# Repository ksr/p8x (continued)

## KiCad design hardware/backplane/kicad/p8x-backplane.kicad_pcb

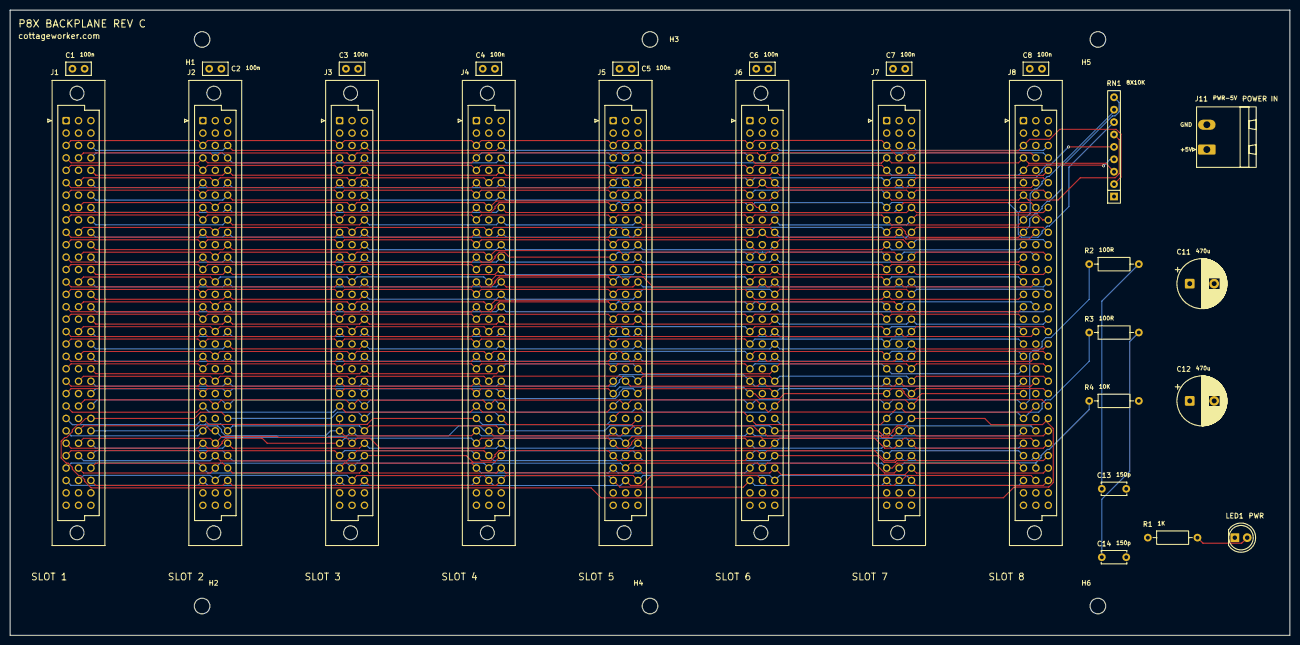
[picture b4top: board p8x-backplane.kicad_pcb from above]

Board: 4 copper layers, 262.0 x 128.0 mm, 33 parts (0 on the bottom side), 77 nets.

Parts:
C1, C2, C3, C4, C5, C6, C7, C8: 100nF; C_Disc_D5.0mm_W2.5mm_P2.50mm
C11, C12: 470uF; CP_Radial_D10.0mm_P5.00mm
C13, C14: 150pF; C_Disc_D5.0mm_W2.5mm_P5.00mm
H1, H2, H3, H4, H5, H6: MountingHole_3.2mm_M3
J1: SLOT1; DIN41612_C_3x32_Female_Vertical_THT
J2: SLOT2; DIN41612_C_3x32_Female_Vertical_THT
J3: SLOT3; DIN41612_C_3x32_Female_Vertical_THT
J4: SLOT4; DIN41612_C_3x32_Female_Vertical_THT
J5: SLOT5; DIN41612_C_3x32_Female_Vertical_THT
J6: SLOT6; DIN41612_C_3x32_Female_Vertical_THT
J7: SLOT7; DIN41612_C_3x32_Female_Vertical_THT
J8: SLOT8; DIN41612_C_3x32_Female_Vertical_THT
J11: PWR-5V; PhoenixContact_MSTBA_2,5_2-G-5,08_1x02_P5.08mm_Horizontal
LED1: PWR; LED_D5.0mm
R1: 1K; R_Axial_DIN0207_L6.3mm_D2.5mm_P10.16mm_Horizontal
R2, R3: 100R; R_Axial_DIN0207_L6.3mm_D2.5mm_P10.16mm_Horizontal
R4: 10K; R_Axial_DIN0207_L6.3mm_D2.5mm_P10.16mm_Horizontal
RN1: 8X10K; R_Array_SIP9

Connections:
-RES: J1.a11, J2.a11, J3.a11, J4.a11, J5.a11, J6.a11, J7.a11, J8.a11
A0: J1.c3, J2.c3, J3.c3, J4.c3, J5.c3, J6.c3, J7.c3, J8.c3
A1: J1.c4, J2.c4, J3.c4, J4.c4, J5.c4, J6.c4, J7.c4, J8.c4
A2: J1.c5, J2.c5, J3.c5, J4.c5, J5.c5, J6.c5, J7.c5, J8.c5
A3: J1.c6, J2.c6, J3.c6, J4.c6, J5.c6, J6.c6, J7.c6, J8.c6
A4: J1.c7, J2.c7, J3.c7, J4.c7, J5.c7, J6.c7, J7.c7, J8.c7
A5: J1.c8, J2.c8, J3.c8, J4.c8, J5.c8, J6.c8, J7.c8, J8.c8
A6: J1.c9, J2.c9, J3.c9, J4.c9, J5.c9, J6.c9, J7.c9, J8.c9
A7: J1.c10, J2.c10, J3.c10, J4.c10, J5.c10, J6.c10, J7.c10, J8.c10
A8: J1.c11, J2.c11, J3.c11, J4.c11, J5.c11, J6.c11, J7.c11, J8.c11
A9: J1.c12, J2.c12, J3.c12, J4.c12, J5.c12, J6.c12, J7.c12, J8.c12
A10: J1.c13, J2.c13, J3.c13, J4.c13, J5.c13, J6.c13, J7.c13, J8.c13
A11: J1.c14, J2.c14, J3.c14, J4.c14, J5.c14, J6.c14, J7.c14, J8.c14
A12: J1.c15, J2.c15, J3.c15, J4.c15, J5.c15, J6.c15, J7.c15, J8.c15
A13: J1.c16, J2.c16, J3.c16, J4.c16, J5.c16, J6.c16, J7.c16, J8.c16
A14: J1.c17, J2.c17, J3.c17, J4.c17, J5.c17, J6.c17, J7.c17, J8.c17
A15: J1.c18, J2.c18, J3.c18, J4.c18, J5.c18, J6.c18, J7.c18, J8.c18
ALUM: J1.c23, J2.c23, J3.c23, J4.c23, J5.c23, J6.c23, J7.c23, J8.c23
ALUS0: J1.c19, J2.c19, J3.c19, J4.c19, J5.c19, J6.c19, J7.c19, J8.c19
ALUS1: J1.c20, J2.c20, J3.c20, J4.c20, J5.c20, J6.c20, J7.c20, J8.c20
ALUS2: J1.c21, J2.c21, J3.c21, J4.c21, J5.c21, J6.c21, J7.c21, J8.c21
ALUS3: J1.c22, J2.c22, J3.c22, J4.c22, J5.c22, J6.c22, J7.c22, J8.c22
BSEL: J1.b28, J2.b28, J3.b28, J4.b28, J5.b28, J6.b28, J7.b28, J8.b28
CIN: J1.c24, J2.c24, J3.c24, J4.c24, J5.c24, J6.c24, J7.c24, J8.c24
CLK: J1.a24, J2.a24, J3.a24, J4.a24, J5.a24, J6.a24, J7.a24, J8.a24, R2.1
CLKB: J1.a25, J2.a25, J3.a25, J4.a25, J5.a25, J6.a25, J7.a25, J8.a25, R3.1
CLKB_T: C14.1, R3.2
CLK_T: C13.1, R2.2
CLRC: J1.b27, J2.b27, J3.b27, J4.b27, J5.b27, J6.b27, J7.b27, J8.b27
D0: J1.a3, J2.a3, J3.a3, J4.a3, J5.a3, J6.a3, J7.a3, J8.a3, RN1.2
D1: J1.a4, J2.a4, J3.a4, J4.a4, J5.a4, J6.a4, J7.a4, J8.a4, RN1.3
D2: J1.a5, J2.a5, J3.a5, J4.a5, J5.a5, J6.a5, J7.a5, J8.a5, RN1.4
D3: J1.a6, J2.a6, J3.a6, J4.a6, J5.a6, J6.a6, J7.a6, J8.a6, RN1.5
D4: J1.a7, J2.a7, J3.a7, J4.a7, J5.a7, J6.a7, J7.a7, J8.a7, RN1.6
D5: J1.a8, J2.a8, J3.a8, J4.a8, J5.a8, J6.a8, J7.a8, J8.a8, RN1.7
D6: J1.a9, J2.a9, J3.a9, J4.a9, J5.a9, J6.a9, J7.a9, J8.a9, RN1.8
D7: J1.a10, J2.a10, J3.a10, J4.a10, J5.a10, J6.a10, J7.a10, J8.a10, RN1.9
DLD0: J1.a16, J2.a16, J3.a16, J4.a16, J5.a16, J6.a16, J7.a16, J8.a16
DLD1: J1.a17, J2.a17, J3.a17, J4.a17, J5.a17, J6.a17, J7.a17, J8.a17
DLD2: J1.a18, J2.a18, J3.a18, J4.a18, J5.a18, J6.a18, J7.a18, J8.a18
DLD3: J1.a19, J2.a19, J3.a19, J4.a19, J5.a19, J6.a19, J7.a19, J8.a19
DOE0: J1.a12, J2.a12, J3.a12, J4.a12, J5.a12, J6.a12, J7.a12, J8.a12
DOE1: J1.a13, J2.a13, J3.a13, J4.a13, J5.a13, J6.a13, J7.a13, J8.a13
DOE2: J1.a14, J2.a14, J3.a14, J4.a14, J5.a14, J6.a14, J7.a14, J8.a14
DOE3: J1.a15, J2.a15, J3.a15, J4.a15, J5.a15, J6.a15, J7.a15, J8.a15
FC: J1.a27, J2.a27, J3.a27, J4.a27, J5.a27, J6.a27, J7.a27, J8.a27
FN: J1.a29, J2.a29, J3.a29, J4.a29, J5.a29, J6.a29, J7.a29, J8.a29
FV: J1.a30, J2.a30, J3.a30, J4.a30, J5.a30, J6.a30, J7.a30, J8.a30
FZ: J1.a28, J2.a28, J3.a28, J4.a28, J5.a28, J6.a28, J7.a28, J8.a28
GND: C1.2, C2.2, C3.2, C4.2, C5.2, C6.2, C7.2, C8.2, C11.2, C12.2, C13.2, C14.2, J1.a31, J1.a32, J1.b3, J1.b5, J1.b7, J1.b9, J1.b11, J1.b13, J1.b15, J1.b17, J1.b19, J1.b21, J1.b23, J1.b25, J1.b31, J1.b32, J1.c31, J1.c32, J2.a31, J2.a32, J2.b3, J2.b5, J2.b7, J2.b9, J2.b11, J2.b13, J2.b15, J2.b17, J2.b19, J2.b21, J2.b23, J2.b25, J2.b31, J2.b32, J2.c31, J2.c32, J3.a31, J3.a32, J3.b3, J3.b5, J3.b7, J3.b9, J3.b11, J3.b13, J3.b15, J3.b17, J3.b19, J3.b21, J3.b23, J3.b25, J3.b31, J3.b32, J3.c31, J3.c32, J4.a31, J4.a32, J4.b3, J4.b5, J4.b7, J4.b9, J4.b11, J4.b13, J4.b15, J4.b17, J4.b19, J4.b21, J4.b23, J4.b25, J4.b31, J4.b32, J4.c31, J4.c32, J5.a31, J5.a32, J5.b3, J5.b5, J5.b7, J5.b9, J5.b11, J5.b13, J5.b15, J5.b17, J5.b19, J5.b21, J5.b23, J5.b25, J5.b31, J5.b32, J5.c31, J5.c32, J6.a31, J6.a32, J6.b3, J6.b5, J6.b7, J6.b9, J6.b11, J6.b13, J6.b15, J6.b17, J6.b19, J6.b21, J6.b23, J6.b25, J6.b31, J6.b32, J6.c31, J6.c32, J7.a31, J7.a32, J7.b3, J7.b5, J7.b7, J7.b9, J7.b11, J7.b13, J7.b15, J7.b17, J7.b19, J7.b21, J7.b23, J7.b25, J7.b31, J7.b32, J7.c31, J7.c32, J8.a31, J8.a32, J8.b3, J8.b5, J8.b7, J8.b9, J8.b11, J8.b13, J8.b15, J8.b17, J8.b19, J8.b21, J8.b23, J8.b25, J8.b31, J8.b32, J8.c31, J8.c32, J11.2, LED1.1
IRQ: J1.b29, J2.b29, J3.b29, J4.b29, J5.b29, J6.b29, J7.b29, J8.b29, R4.1
LDF: J1.a26, J2.a26, J3.a26, J4.a26, J5.a26, J6.a26, J7.a26, J8.a26
LDZN: J1.c28, J2.c28, J3.c28, J4.c28, J5.c28, J6.c28, J7.c28, J8.c28
LED_A: LED1.2, R1.2
PDEC: J1.a23, J2.a23, J3.a23, J4.a23, J5.a23, J6.a23, J7.a23, J8.a23
PINC: J1.a22, J2.a22, J3.a22, J4.a22, J5.a22, J6.a22, J7.a22, J8.a22
PSEL0: J1.a20, J2.a20, J3.a20, J4.a20, J5.a20, J6.a20, J7.a20, J8.a20
PSEL1: J1.a21, J2.a21, J3.a21, J4.a21, J5.a21, J6.a21, J7.a21, J8.a21
PSEL2: J1.c27, J2.c27, J3.c27, J4.c27, J5.c27, J6.c27, J7.c27, J8.c27
SETC: J1.c30, J2.c30, J3.c30, J4.c30, J5.c30, J6.c30, J7.c30, J8.c30
SH0: J1.c25, J2.c25, J3.c25, J4.c25, J5.c25, J6.c25, J7.c25, J8.c25
SH1: J1.c26, J2.c26, J3.c26, J4.c26, J5.c26, J6.c26, J7.c26, J8.c26
SHCIN: J1.c29, J2.c29, J3.c29, J4.c29, J5.c29, J6.c29, J7.c29, J8.c29
SPARE11: J1.b30, J2.b30, J3.b30, J4.b30, J5.b30, J6.b30, J7.b30, J8.b30
SPARE12: J1.b4, J2.b4, J3.b4, J4.b4, J5.b4, J6.b4, J7.b4, J8.b4
SPARE13: J1.b6, J2.b6, J3.b6, J4.b6, J5.b6, J6.b6, J7.b6, J8.b6
SPARE14: J1.b8, J2.b8, J3.b8, J4.b8, J5.b8, J6.b8, J7.b8, J8.b8
SPARE15: J1.b10, J2.b10, J3.b10, J4.b10, J5.b10, J6.b10, J7.b10, J8.b10
SPARE16: J1.b12, J2.b12, J3.b12, J4.b12, J5.b12, J6.b12, J7.b12, J8.b12
SPARE17: J1.b14, J2.b14, J3.b14, J4.b14, J5.b14, J6.b14, J7.b14, J8.b14
SPARE18: J1.b16, J2.b16, J3.b16, J4.b16, J5.b16, J6.b16, J7.b16, J8.b16
SPARE19: J1.b18, J2.b18, J3.b18, J4.b18, J5.b18, J6.b18, J7.b18, J8.b18
SPARE20: J1.b20, J2.b20, J3.b20, J4.b20, J5.b20, J6.b20, J7.b20, J8.b20
SPARE21: J1.b22, J2.b22, J3.b22, J4.b22, J5.b22, J6.b22, J7.b22, J8.b22
SPARE22: J1.b24, J2.b24, J3.b24, J4.b24, J5.b24, J6.b24, J7.b24, J8.b24
SPARE23: J1.b26, J2.b26, J3.b26, J4.b26, J5.b26, J6.b26, J7.b26, J8.b26
VCC: C1.1, C2.1, C3.1, C4.1, C5.1, C6.1, C7.1, C8.1, C11.1, C12.1, J1.a1, J1.a2, J1.b1, J1.b2, J1.c1, J1.c2, J2.a1, J2.a2, J2.b1, J2.b2, J2.c1, J2.c2, J3.a1, J3.a2, J3.b1, J3.b2, J3.c1, J3.c2, J4.a1, J4.a2, J4.b1, J4.b2, J4.c1, J4.c2, J5.a1, J5.a2, J5.b1, J5.b2, J5.c1, J5.c2, J6.a1, J6.a2, J6.b1, J6.b2, J6.c1, J6.c2, J7.a1, J7.a2, J7.b1, J7.b2, J7.c1, J7.c2, J8.a1, J8.a2, J8.b1, J8.b2, J8.c1, J8.c2, J11.1, R1.1, R4.2, RN1.1

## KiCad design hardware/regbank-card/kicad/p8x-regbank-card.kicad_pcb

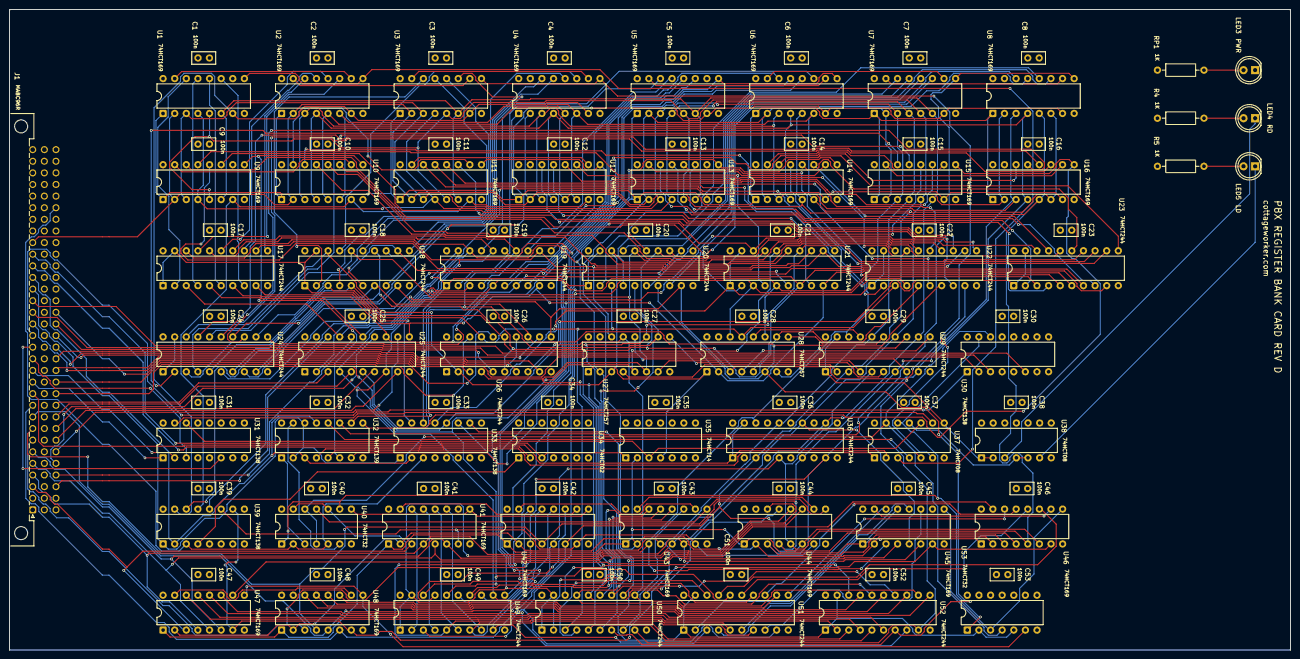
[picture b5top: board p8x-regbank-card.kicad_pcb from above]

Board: 4 copper layers, 280.0 x 140.0 mm, 113 parts (0 on the bottom side), 221 nets.

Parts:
C1, C2, C3, C4, C5, C6, C7, C8, C9, C10, C11, C12, C13, C14, C15, C16, C17, C18, C19, C20, C21, C22, C23, C24, C25, C26, C27, C28, C29, C30, C31, C32, C33, C34, C35, C36, C37, C38, C39, C40, C41, C42, C43, C44, C45, C46, C47, C48, C49, C50, C51, C52, C53: 100nF; C_Disc_D5.0mm_W2.5mm_P2.50mm
J1: MABC96R; DIN41612_C_3x32_Male_Horizontal_THT
LED3, LED4: GRN; LED_D5.0mm
LED5: YEL; LED_D5.0mm
R4, R5: 1K; R_Axial_DIN0207_L6.3mm_D2.5mm_P10.16mm_Horizontal
RP1: 1K; R_Axial_DIN0207_L6.3mm_D2.5mm_P10.16mm_Horizontal
U1, U2, U3, U4, U5, U6, U7, U8, U9, U10, U11, U12, U13, U14, U15, U16, U41, U42, U43, U44, U45, U46, U47, U48: 74HCT169; DIP-16_W7.62mm
U17, U18, U19, U20, U21, U22, U23, U24, U25, U26, U29, U36, U49, U50, U51, U52: 74HCT244; DIP-20_W7.62mm
U27, U28: 74HCT257; DIP-16_W7.62mm
U30, U31, U33, U39: 74HCT138; DIP-16_W7.62mm
U32: 74HCT139; DIP-16_W7.62mm
U34: 74HCT02; DIP-14_W7.62mm
U35: 74HCT14; DIP-14_W7.62mm
U37, U38: 74HCT08; DIP-14_W7.62mm
U40, U53: 74HCT32; DIP-14_W7.62mm

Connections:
-CNT0: U1.7, U2.7, U3.7, U4.7, U39.15
-CNT1: U5.7, U6.7, U7.7, U8.7, U39.14
-CNT2: U9.7, U10.7, U11.7, U12.7, U39.13
-CNT3: U13.7, U14.7, U15.7, U16.7, U39.12
-CNT4: U39.11, U41.7, U42.7, U43.7, U44.7
-CNT5: U39.10, U45.7, U46.7, U47.7, U48.7
-LDH: U30.14, U37.13, U40.4, U40.12, U53.4
-LDH0: U32.12, U37.4
-LDH0E: U3.9, U4.9, U37.6
-LDH1: U7.9, U8.9, U32.11
-LDH2: U11.9, U12.9, U32.10
-LDH3: U15.9, U16.9, U32.9
-LDH4: U40.11, U43.9, U44.9
-LDH5: U47.9, U48.9, U53.6
-LDHG: U32.15, U40.6
-LDL: U30.15, U37.12, U40.1, U40.9, U53.1
-LDL0: U32.4, U37.1
-LDL0E: U1.9, U2.9, U37.3
-LDL1: U5.9, U6.9, U32.5
-LDL2: U9.9, U10.9, U32.6
-LDL3: U13.9, U14.9, U32.7
-LDL4: U40.8, U41.9, U42.9
-LDL5: U45.9, U46.9, U53.3
-LDLG: U32.1, U40.3
-LDP: U37.11, U38.4, U38.5
-POE: U29.1, U29.19, U37.8, U38.1, U38.2
-POEH: U31.14, U35.3, U37.10
-POEL: U31.15, U37.9
-RES: J1.a11, U36.1, U36.19, U37.2, U37.5
-SEL0: U17.1, U17.19, U18.1, U18.19, U33.15
-SEL1: U19.1, U19.19, U20.1, U20.19, U33.14
-SEL2: U21.1, U21.19, U22.1, U22.19, U33.13
-SEL3: U23.1, U23.19, U24.1, U24.19, U33.12
-SEL4: U33.11, U40.10, U40.13, U49.1, U49.19, U50.1, U50.19
-SEL5: U33.10, U51.1, U51.19, U52.1, U52.19, U53.2, U53.5
A0: J1.c3, U25.18
A1: J1.c4, U25.16
A2: J1.c5, U25.14
A3: J1.c6, U25.12
A4: J1.c7, U25.9
A5: J1.c8, U25.7
A6: J1.c9, U25.5
A7: J1.c10, U25.3
A8: J1.c11, U26.18
A9: J1.c12, U26.16
A10: J1.c13, U26.14
A11: J1.c14, U26.12
A12: J1.c15, U26.9
A13: J1.c16, U26.7
A14: J1.c17, U26.5
A15: J1.c18, U26.3
CLK: J1.a24, U1.2, U2.2, U3.2, U4.2, U5.2, U6.2, U7.2, U8.2, U9.2, U10.2, U11.2, U12.2, U13.2, U14.2, U15.2, U16.2, U41.2, U42.2, U43.2, U44.2, U45.2, U46.2, U47.2, U48.2
CNTN: U34.1, U39.4
D0: J1.a3, U1.3, U3.3, U5.3, U7.3, U9.3, U11.3, U13.3, U15.3, U29.18, U36.18, U41.3, U43.3, U45.3, U47.3
D1: J1.a4, U1.4, U3.4, U5.4, U7.4, U9.4, U11.4, U13.4, U15.4, U29.16, U36.16, U41.4, U43.4, U45.4, U47.4
D2: J1.a5, U1.5, U3.5, U5.5, U7.5, U9.5, U11.5, U13.5, U15.5, U29.14, U36.14, U41.5, U43.5, U45.5, U47.5
D3: J1.a6, U1.6, U3.6, U5.6, U7.6, U9.6, U11.6, U13.6, U15.6, U29.12, U36.12, U41.6, U43.6, U45.6, U47.6
D4: J1.a7, U2.3, U4.3, U6.3, U8.3, U10.3, U12.3, U14.3, U16.3, U29.9, U36.9, U42.3, U44.3, U46.3, U48.3
D5: J1.a8, U2.4, U4.4, U6.4, U8.4, U10.4, U12.4, U14.4, U16.4, U29.7, U36.7, U42.4, U44.4, U46.4, U48.4
D6: J1.a9, U2.5, U4.5, U6.5, U8.5, U10.5, U12.5, U14.5, U16.5, U29.5, U36.5, U42.5, U44.5, U46.5, U48.5
D7: J1.a10, U2.6, U4.6, U6.6, U8.6, U10.6, U12.6, U14.6, U16.6, U29.3, U36.3, U42.6, U44.6, U46.6, U48.6
DLD0: J1.a16, U30.1
DLD1: J1.a17, U30.2
DLD2: J1.a18, U30.3
DLD3: J1.a19, U30.6
DOE0: J1.a12, U31.1
DOE1: J1.a13, U31.2
DOE2: J1.a14, U31.3
DOE3: J1.a15, U31.6
GND: C1.2, C2.2, C3.2, C4.2, C5.2, C6.2, C7.2, C8.2, C9.2, C10.2, C11.2, C12.2, C13.2, C14.2, C15.2, C16.2, C17.2, C18.2, C19.2, C20.2, C21.2, C22.2, C23.2, C24.2, C25.2, C26.2, C27.2, C28.2, C29.2, C30.2, C31.2, C32.2, C33.2, C34.2, C35.2, C36.2, C37.2, C38.2, C39.2, C40.2, C41.2, C42.2, C43.2, C44.2, C45.2, C46.2, C47.2, C48.2, C49.2, C50.2, C51.2, C52.2, C53.2, J1.a31, J1.a32, J1.b3, J1.b5, J1.b7, J1.b9, J1.b11, J1.b13, J1.b15, J1.b17, J1.b19, J1.b21, J1.b23, J1.b25, J1.b31, J1.b32, J1.c31, J1.c32, LED3.1, U1.8, U1.10, U2.8, U3.8, U4.8, U5.8, U5.10, U6.8, U7.8, U8.8, U9.8, U9.10, U10.8, U11.8, U12.8, U13.8, U13.10, U14.8, U15.8, U16.8, U17.10, U18.10, U19.10, U20.10, U21.10, U22.10, U23.10, U24.10, U25.1, U25.10, U25.19, U26.1, U26.10, U26.19, U27.8, U27.15, U28.8, U28.15, U29.10, U30.4, U30.5, U30.8, U31.4, U31.5, U31.8, U32.8, U33.4, U33.5, U33.8, U34.5, U34.6, U34.7, U34.8, U34.9, U34.11, U34.12, U35.5, U35.7, U35.9, U35.11, U35.13, U36.2, U36.4, U36.6, U36.8, U36.10, U36.11, U36.13, U36.15, U36.17, U37.7, U38.7, U38.9, U38.10, U38.12, U38.13, U39.5, U39.8, U40.7, U41.8, U41.10, U42.8, U43.8, U44.8, U45.8, U45.10, U46.8, U47.8, U48.8, U49.10, U50.10, U51.10, U52.10, U53.7, U53.9, U53.10, U53.12, U53.13
LDK: LED5.1, U38.6
LEDLD: LED5.2, R5.2
LEDP: LED3.2, RP1.2
LEDRD: LED4.2, R4.2
PB0: U17.18, U19.18, U21.18, U23.18, U25.2, U27.2, U49.18, U51.18
PB1: U17.16, U19.16, U21.16, U23.16, U25.4, U27.5, U49.16, U51.16
PB2: U17.14, U19.14, U21.14, U23.14, U25.6, U27.11, U49.14, U51.14
PB3: U17.12, U19.12, U21.12, U23.12, U25.8, U27.14, U49.12, U51.12
PB4: U17.9, U19.9, U21.9, U23.9, U25.11, U28.2, U49.9, U51.9
PB5: U17.7, U19.7, U21.7, U23.7, U25.13, U28.5, U49.7, U51.7
PB6: U17.5, U19.5, U21.5, U23.5, U25.15, U28.11, U49.5, U51.5
PB7: U17.3, U19.3, U21.3, U23.3, U25.17, U28.14, U49.3, U51.3
PB8: U18.18, U20.18, U22.18, U24.18, U26.2, U27.3, U50.18, U52.18
PB9: U18.16, U20.16, U22.16, U24.16, U26.4, U27.6, U50.16, U52.16
PB10: U18.14, U20.14, U22.14, U24.14, U26.6, U27.10, U50.14, U52.14
PB11: U18.12, U20.12, U22.12, U24.12, U26.8, U27.13, U50.12, U52.12
PB12: U18.9, U20.9, U22.9, U24.9, U26.11, U28.3, U50.9, U52.9
PB13: U18.7, U20.7, U22.7, U24.7, U26.13, U28.6, U50.7, U52.7
PB14: U18.5, U20.5, U22.5, U24.5, U26.15, U28.10, U50.5, U52.5
PB15: U18.3, U20.3, U22.3, U24.3, U26.17, U28.13, U50.3, U52.3
PDEC: J1.a23, U34.3, U35.1
PINC: J1.a22, U34.2
POEHP: U27.1, U28.1, U35.4
PQ0_0: U1.14, U17.2
PQ0_1: U1.13, U17.4
PQ0_2: U1.12, U17.6
PQ0_3: U1.11, U17.8
PQ0_4: U2.14, U17.11
PQ0_5: U2.13, U17.13
PQ0_6: U2.12, U17.15
PQ0_7: U2.11, U17.17
PQ0_8: U3.14, U18.2
PQ0_9: U3.13, U18.4
PQ0_10: U3.12, U18.6
PQ0_11: U3.11, U18.8
PQ0_12: U4.14, U18.11
PQ0_13: U4.13, U18.13
PQ0_14: U4.12, U18.15
PQ0_15: U4.11, U18.17
PQ1_0: U5.14, U19.2
PQ1_1: U5.13, U19.4
PQ1_2: U5.12, U19.6
PQ1_3: U5.11, U19.8
PQ1_4: U6.14, U19.11
PQ1_5: U6.13, U19.13
PQ1_6: U6.12, U19.15
PQ1_7: U6.11, U19.17
PQ1_8: U7.14, U20.2
PQ1_9: U7.13, U20.4
PQ1_10: U7.12, U20.6
PQ1_11: U7.11, U20.8
PQ1_12: U8.14, U20.11
PQ1_13: U8.13, U20.13
PQ1_14: U8.12, U20.15
PQ1_15: U8.11, U20.17
PQ2_0: U9.14, U21.2
PQ2_1: U9.13, U21.4
PQ2_2: U9.12, U21.6
PQ2_3: U9.11, U21.8
PQ2_4: U10.14, U21.11
PQ2_5: U10.13, U21.13
PQ2_6: U10.12, U21.15
PQ2_7: U10.11, U21.17
PQ2_8: U11.14, U22.2
PQ2_9: U11.13, U22.4
PQ2_10: U11.12, U22.6
PQ2_11: U11.11, U22.8
PQ2_12: U12.14, U22.11
PQ2_13: U12.13, U22.13
PQ2_14: U12.12, U22.15
PQ2_15: U12.11, U22.17
PQ3_0: U13.14, U23.2
PQ3_1: U13.13, U23.4
PQ3_2: U13.12, U23.6
PQ3_3: U13.11, U23.8
PQ3_4: U14.14, U23.11
PQ3_5: U14.13, U23.13
PQ3_6: U14.12, U23.15
PQ3_7: U14.11, U23.17
PQ3_8: U15.14, U24.2
PQ3_9: U15.13, U24.4
PQ3_10: U15.12, U24.6
PQ3_11: U15.11, U24.8
PQ3_12: U16.14, U24.11
PQ3_13: U16.13, U24.13
PQ3_14: U16.12, U24.15
PQ3_15: U16.11, U24.17
PQ4_0: U41.14, U49.2
PQ4_1: U41.13, U49.4
PQ4_2: U41.12, U49.6
PQ4_3: U41.11, U49.8
PQ4_4: U42.14, U49.11
PQ4_5: U42.13, U49.13
PQ4_6: U42.12, U49.15
PQ4_7: U42.11, U49.17
PQ4_8: U43.14, U50.2
PQ4_9: U43.13, U50.4
PQ4_10: U43.12, U50.6
PQ4_11: U43.11, U50.8
PQ4_12: U44.14, U50.11
PQ4_13: U44.13, U50.13
PQ4_14: U44.12, U50.15
PQ4_15: U44.11, U50.17
PQ5_0: U45.14, U51.2
PQ5_1: U45.13, U51.4
PQ5_2: U45.12, U51.6
PQ5_3: U45.11, U51.8
PQ5_4: U46.14, U51.11
PQ5_5: U46.13, U51.13
PQ5_6: U46.12, U51.15
PQ5_7: U46.11, U51.17
PQ5_8: U47.14, U52.2
PQ5_9: U47.13, U52.4
PQ5_10: U47.12, U52.6
PQ5_11: U47.11, U52.8
PQ5_12: U48.14, U52.11
PQ5_13: U48.13, U52.13
PQ5_14: U48.12, U52.15
PQ5_15: U48.11, U52.17
PSEL0: J1.a20, U32.2, U32.14, U33.1, U39.1
PSEL1: J1.a21, U32.3, U32.13, U33.2, U39.2
PSEL2: J1.c27, U33.3, U39.3, U40.2, U40.5
RB0: U27.4, U29.2
RB1: U27.7, U29.4
RB2: U27.9, U29.6
RB3: U27.12, U29.8
RB4: U28.4, U29.11
RB5: U28.7, U29.13
RB6: U28.9, U29.15
RB7: U28.12, U29.17
RC0_0: U1.15, U2.10
RC0_1: U2.15, U3.10
RC0_2: U3.15, U4.10
RC1_0: U5.15, U6.10
RC1_1: U6.15, U7.10
RC1_2: U7.15, U8.10
RC2_0: U9.15, U10.10
RC2_1: U10.15, U11.10
RC2_2: U11.15, U12.10
RC3_0: U13.15, U14.10
RC3_1: U14.15, U15.10
RC3_2: U15.15, U16.10
RC4_0: U41.15, U42.10
RC4_1: U42.15, U43.10
RC4_2: U43.15, U44.10
RC5_0: U45.15, U46.10
RC5_1: U46.15, U47.10
RC5_2: U47.15, U48.10
RDK: LED4.1, U38.3
UDB: U1.1, U2.1, U3.1, U4.1, U5.1, U6.1, U7.1, U8.1, U9.1, U10.1, U11.1, U12.1, U13.1, U14.1, U15.1, U16.1, U35.2, U41.1, U42.1, U43.1, U44.1, U45.1, U46.1, U47.1, U48.1
VCC: C1.1, C2.1, C3.1, C4.1, C5.1, C6.1, C7.1, C8.1, C9.1, C10.1, C11.1, C12.1, C13.1, C14.1, C15.1, C16.1, C17.1, C18.1, C19.1, C20.1, C21.1, C22.1, C23.1, C24.1, C25.1, C26.1, C27.1, C28.1, C29.1, C30.1, C31.1, C32.1, C33.1, C34.1, C35.1, C36.1, C37.1, C38.1, C39.1, C40.1, C41.1, C42.1, C43.1, C44.1, C45.1, C46.1, C47.1, C48.1, C49.1, C50.1, C51.1, C52.1, C53.1, J1.a1, J1.a2, J1.b1, J1.b2, J1.c1, J1.c2, R4.1, R5.1, RP1.1, U1.16, U2.16, U3.16, U4.16, U5.16, U6.16, U7.16, U8.16, U9.16, U10.16, U11.16, U12.16, U13.16, U14.16, U15.16, U16.16, U17.20, U18.20, U19.20, U20.20, U21.20, U22.20, U23.20, U24.20, U25.20, U26.20, U27.16, U28.16, U29.20, U30.16, U31.16, U32.16, U33.6, U33.16, U34.14, U35.14, U36.20, U37.14, U38.14, U39.6, U39.16, U40.14, U41.16, U42.16, U43.16, U44.16, U45.16, U46.16, U47.16, U48.16, U49.20, U50.20, U51.20, U52.20, U53.14

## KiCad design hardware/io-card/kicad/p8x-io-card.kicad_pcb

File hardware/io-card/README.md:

# I/O Card

> **Theory of operation:** [p8x-io-card-theory.md](p8x-io-card-theory.md) — deep walkthrough of inputs/outputs, signal flow, and logic.

All memory-mapped I/O lives here: an 8-switch input port, an 8-LED output port,
**two** RS-232 serial channels via 6850 ACIAs (rev B), and a passive **bus-monitor**
LED display that turns the machine into an Altair-style "watch it think" front panel.

> **Rev B (2026-09-19)** — the routed KiCad board in [`kicad/`](kicad/README.md)
> (not yet fabricated) adds a second 6850 (**U17**, ACIA2 at `$FF08/09`, the
> Kermit / serial-terminal port) on the MAX232's second channel, with its E-gate
> inverter in **U18** (74HCT14). Each channel has its own **DB9** socket and a
> 2×3 jumper block that swaps RX/TX (straight or null-modem). A DS1302 real-time
> clock (**U16**) is provisioned but not fitted (DNP): it is a bit-banged 3-wire
> part on header J3, not memory-mapped. The text below describes the rev A
> circuit, which rev B keeps.

| Address | Port |
|---------|------|
| `$FF00` | Switch input — 8 toggle switches → data bus on read |
| `$FF02` | LED output — 74374 latch → 8 LEDs on write |
| `$FF04` | 6850 ACIA control/status |
| `$FF05` | 6850 ACIA data (RS-232 TX/RX) |
| `$FF08` | ACIA2 control/status (rev B) |
| `$FF09` | ACIA2 data (rev B) |

> This README describes the circuit as actually built in
> [`generators/gen_eagle.py`](../../generators/gen_eagle.py). See
> [p8x-system-design.md §7](../../docs/p8x-system-design.md) for the overview and
> [p8x-bus-definition.md](../backplane/p8x-bus-definition.md) for bus pins.

## Chip inventory

| Ref | Device | Role |
|-----|--------|------|
| U1 | 7430 | 8-input NAND — I/O page ($FFxx) detector |
| U2 | 74138 | Port decoder (A1–A3 → up to 8 port selects) |
| U3 | 74138 | DOE decoder (read enable) |
| U4 | 74138 | DLD decoder (write strobe) |
| U5 | 74HCT32 | OR glue (read/write strobe gating) |
| U6 | 74HCT08 | AND glue (ACIA enable) |
| U7 | 74161 | Baud-rate divider |
| U8 | MAX232 | RS-232 level shifter (the one non-TTL part) |
| U9 | 74244 | Switch-input buffer |
| U10 | 74374 | LED output latch |
| U11–U13 | 74244 | Bus monitors — A0–7, A8–15, D0–7 |
| U14 | 6850 | ACIA (asynchronous serial) |
| U15 | 74HCT00 | NAND glue |
| U16 | DS1302 | Real-time clock, DNP (rev B; 3-wire on J3, not memory-mapped) |
| U17 | 6850 | ACIA2 at `$FF08/09` (rev B) |
| U18 | 74HCT14 | Inverter — ACIA2 enable gate (rev B) |
| X2 | 2.4576 MHz osc | Baud clock source |

## How it works

### Port decoding
U1 (7430) detects the `$FFxx` page exactly as on the memory card. Within the page,
U2 (74138) decodes the low address lines into individual port selects (`-P0`, `-P1`,
`-P2`, …). Read vs write comes from the DOE decoder (U3 → `-RD`) and DLD decoder
(U4 → `-MEMW`), gated in U5/U6 into per-port read/write strobes.

### Switch input ($FF00)
Eight toggle switches with a SIP pull-up network feed a 74244 (U9). On a read of
`$FF00`, U9 is enabled and drives the switch states onto D0–D7.

### LED output ($FF02)
On a write to `$FF02`, the 74374 (U10) latches D0–D7. Its outputs drive an LED bank
through series-resistor networks, so the port value is visible at a glance.

### Serial (6850 ACIA, $FF04–$FF05)
The **6850 ACIA** (U14) handles asynchronous serial. Its enable is the `$FF04/05`
port select gated with the clock (U6/U15) for correct E-clock timing. A **74161**
(U7) divides the dedicated **2.4576 MHz** oscillator (X2) by 16 to make the
TX/RX baud clock. The **MAX232** (U8) — the one concession to non-TTL parts —
converts the ACIA's TTL levels to/from RS-232 ±voltages on the serial header,
using its four external charge-pump capacitors.

### Bus-monitor display (passive)
Three 74244 buffers (U11/U12/U13) permanently sample A0–7, A8–15, and D0–7 and
drive three LED banks. They cost nothing logically — no decode, no bus access —
but combined with the control card's single-step button they let you literally
watch the address and data buses change one microcycle at a time.

## Bus codes this card owns
- **DOE:** 7 = read (the active port drives D0–D7) — shared decode convention with memory
- **DLD:** 7 = write (`MEMW`) — the active port latches D0–D7

## LEDs
PWR (green), IOSEL (yellow — an I/O port is selected), plus the LED output port and
the 24-bit bus-monitor banks.

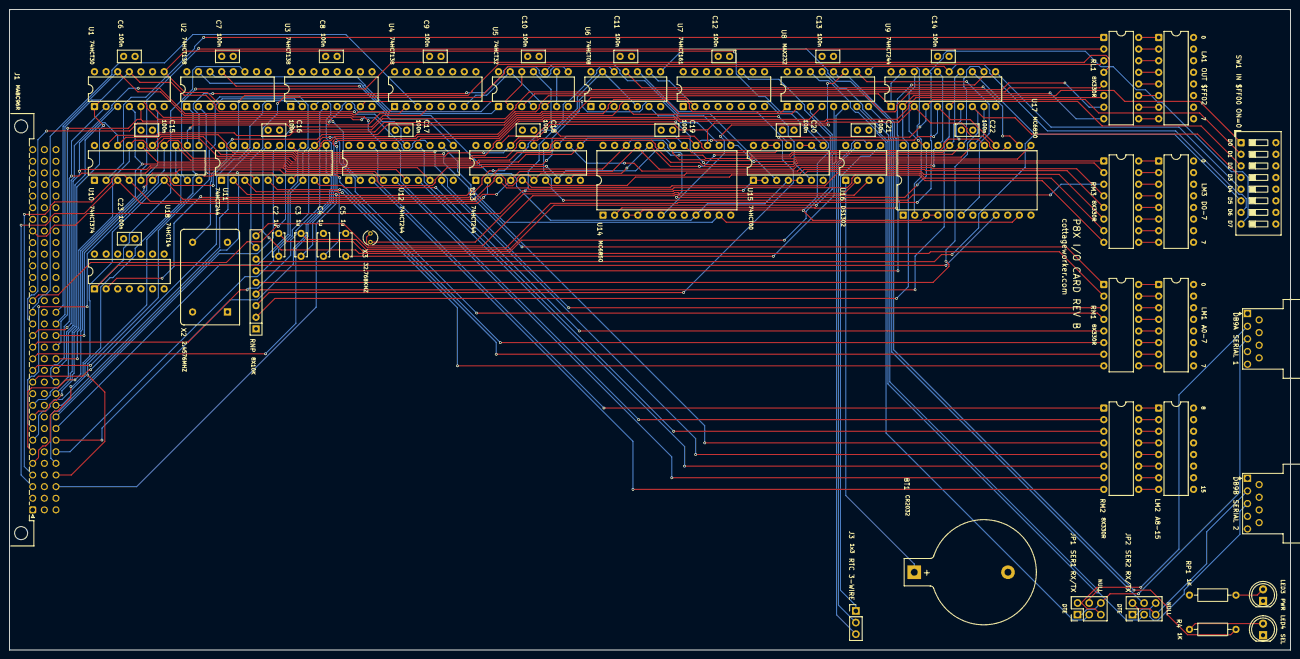
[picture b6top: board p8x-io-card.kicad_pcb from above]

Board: 4 copper layers, 280.0 x 140.0 mm, 63 parts (0 on the bottom side), 154 nets.

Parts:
BT1: CR2032; BatteryHolder_Keystone_103_1x20mm
C2, C3, C4, C5: 1uF; C_Disc_D5.0mm_W2.5mm_P5.00mm
C6, C7, C8, C9, C10, C11, C12, C13, C14, C15, C16, C17, C18, C19, C20, C21, C22, C23: 100nF; C_Disc_D5.0mm_W2.5mm_P2.50mm
DB9A: SERIAL1; DSUB-9_Socket_Horizontal_P2.77x2.54mm_EdgePinOffset9.40mm
DB9B: SERIAL2; DSUB-9_Socket_Horizontal_P2.77x2.54mm_EdgePinOffset9.40mm
J1: MABC96R; DIN41612_C_3x32_Male_Horizontal_THT
J3: 1x3; PinHeader_1x03_P2.54mm_Vertical
JP1: S1 SWAP; PinHeader_2x03_P2.54mm_Vertical
JP2: S2 SWAP; PinHeader_2x03_P2.54mm_Vertical
LA1: 8-LED BAR; DIP-16_W7.62mm
LED3: GRN; LED_D5.0mm
LED4: YEL; LED_D5.0mm
LM1: A0-7; DIP-16_W7.62mm
LM2: A8-15; DIP-16_W7.62mm
LM3: D0-7; DIP-16_W7.62mm
R4: 1K; R_Axial_DIN0207_L6.3mm_D2.5mm_P10.16mm_Horizontal
RL1: 8X330R; DIP-16_W7.62mm
RM1, RM2, RM3: 8X330R; DIP-16_W7.62mm
RNP: 8X10K; R_Array_SIP9
RP1: 1K; R_Axial_DIN0207_L6.3mm_D2.5mm_P10.16mm_Horizontal
SW1: INPUT; SW_DIP_SPSTx08_Slide_9.78x22.5mm_W7.62mm_P2.54mm
U1: 74HCT30; DIP-14_W7.62mm
U2, U3, U4: 74HCT138; DIP-16_W7.62mm
U5: 74HCT32; DIP-14_W7.62mm
U6: 74HCT08; DIP-14_W7.62mm
U7: 74HCT161; DIP-16_W7.62mm
U8: MAX232; DIP-16_W7.62mm
U9, U11, U12, U13: 74HCT244; DIP-20_W7.62mm
U10: 74HCT374; DIP-20_W7.62mm
U14, U17: 6850; DIP-24_W15.24mm
U15: 74HCT00; DIP-14_W7.62mm
U16: DS1302; DIP-8_W7.62mm
U18: 74HCT14; DIP-14_W7.62mm
X2: 2.4576MHZ; Oscillator_DIP-14
X3: 32.768KHZ; Crystal_Round_D3.0mm_Vertical

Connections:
-MEMW: U4.7, U5.5, U5.13, U14.13, U17.13
-P0: U2.15, U5.1
-P1: U2.14, U5.4
-P2: U2.13, U14.9, U15.4, U15.5
-P4: U2.11, U17.9, U18.1
-RD: U3.7, U5.2, U5.12
-SWOE: U5.3, U9.1, U9.19
A0: J1.c3, U11.2, U14.11, U17.11
A1: J1.c4, U2.1, U11.4
A2: J1.c5, U2.2, U11.6
A3: J1.c6, U2.3, U11.8
A4: J1.c7, U11.11
A5: J1.c8, U11.13
A6: J1.c9, U11.15
A7: J1.c10, U11.17
A8: J1.c11, U1.1, U12.2
A9: J1.c12, U1.2, U12.4
A10: J1.c13, U1.3, U12.6
A11: J1.c14, U1.4, U12.8
A12: J1.c15, U1.5, U12.11
A13: J1.c16, U1.6, U12.13
A14: J1.c17, U1.11, U12.15
A15: J1.c18, U1.12, U12.17
ACCP: U6.10, U15.11
BCLK: U7.11, U14.3, U14.4, U17.3, U17.4
BOEISH: U5.11, U15.12, U15.13
BOSC: U7.2, X2.8
C1MN: C2.2, U8.3
C1PN: C2.1, U8.1
C2MN: C3.2, U8.5
C2PN: C3.1, U8.4
CLKB: J1.a25, U6.5, U6.13, U15.1, U15.2
CLKBN: U5.10, U15.3
D0: J1.a3, U9.18, U10.3, U13.2, U14.22, U17.22
D1: J1.a4, U9.16, U10.4, U13.4, U14.21, U17.21
D2: J1.a5, U9.14, U10.7, U13.6, U14.20, U17.20
D3: J1.a6, U9.12, U10.8, U13.8, U14.19, U17.19
D4: J1.a7, U9.9, U10.13, U13.11, U14.18, U17.18
D5: J1.a8, U9.7, U10.14, U13.13, U14.17, U17.17
D6: J1.a9, U9.5, U10.17, U13.15, U14.16, U17.16
D7: J1.a10, U9.3, U10.18, U13.17, U14.15, U17.15
DLD0: J1.a16, U4.1
DLD1: J1.a17, U4.2
DLD2: J1.a18, U4.3
DLD3: J1.a19, U4.4
DOE0: J1.a12, U3.1
DOE1: J1.a13, U3.2
DOE2: J1.a14, U3.3
DOE3: J1.a15, U3.4
E2: U6.11, U17.14
EEN: U6.6, U14.14
GND: BT1.2, C4.2, C5.2, C6.2, C7.2, C8.2, C9.2, C10.2, C11.2, C12.2, C13.2, C14.2, C15.2, C16.2, C17.2, C18.2, C19.2, C20.2, C21.2, C22.2, C23.2, DB9A.5, DB9B.5, J1.a31, J1.a32, J1.b3, J1.b5, J1.b7, J1.b9, J1.b11, J1.b13, J1.b15, J1.b17, J1.b19, J1.b21, J1.b23, J1.b25, J1.b31, J1.b32, J1.c31, J1.c32, LA1.9, LA1.10, LA1.11, LA1.12, LA1.13, LA1.14, LA1.15, LA1.16, LED3.1, LED4.1, LM1.9, LM1.10, LM1.11, LM1.12, LM1.13, LM1.14, LM1.15, LM1.16, LM2.9, LM2.10, LM2.11, LM2.12, LM2.13, LM2.14, LM2.15, LM2.16, LM3.9, LM3.10, LM3.11, LM3.12, LM3.13, LM3.14, LM3.15, LM3.16, SW1.9, SW1.10, SW1.11, SW1.12, SW1.13, SW1.14, SW1.15, SW1.16, U1.7, U2.5, U2.8, U3.5, U3.8, U4.5, U4.8, U5.7, U6.1, U6.2, U6.7, U7.3, U7.4, U7.5, U7.6, U7.8, U8.15, U9.10, U10.1, U10.10, U11.1, U11.10, U11.19, U12.1, U12.10, U12.19, U13.1, U13.10, U13.19, U14.1, U14.23, U14.24, U15.7, U16.4, U17.1, U17.23, U17.24, U18.3, U18.5, U18.7, U18.9, U18.11, U18.13, X2.7
IOPG: U1.8, U2.4, U15.9, U15.10
IOPGN: U6.9, U15.8
LCK: U5.8, U10.11
LED4A: LED4.2, R4.1
LEDP: LED3.2, RP1.2
LP0: RL1.1, U10.2
LP1: RL1.2, U10.5
LP2: RL1.3, U10.6
LP3: RL1.4, U10.9
LP4: RL1.5, U10.12
LP5: RL1.6, U10.15
LP6: RL1.7, U10.16
LP7: RL1.8, U10.19
LR0: LA1.1, RL1.16
LR1: LA1.2, RL1.15
LR2: LA1.3, RL1.14
LR3: LA1.4, RL1.13
LR4: LA1.5, RL1.12
LR5: LA1.6, RL1.11
LR6: LA1.7, RL1.10
LR7: LA1.8, RL1.9
LW1: U5.6, U5.9
MA0: RM1.1, U11.18
MA1: RM1.2, U11.16
MA2: RM1.3, U11.14
MA3: RM1.4, U11.12
MA4: RM1.5, U11.9
MA5: RM1.6, U11.7
MA6: RM1.7, U11.5
MA7: RM1.8, U11.3
MA8: RM2.1, U12.18
MA9: RM2.2, U12.16
MA10: RM2.3, U12.14
MA11: RM2.4, U12.12
MA12: RM2.5, U12.9
MA13: RM2.6, U12.7
MA14: RM2.7, U12.5
MA15: RM2.8, U12.3
MD0: RM3.1, U13.18
MD1: RM3.2, U13.16
MD2: RM3.3, U13.14
MD3: RM3.4, U13.12
MD4: RM3.5, U13.9
MD5: RM3.6, U13.7
MD6: RM3.7, U13.5
MD7: RM3.8, U13.3
ML0_0: LM1.1, RM1.16
ML0_1: LM1.2, RM1.15
ML0_2: LM1.3, RM1.14
ML0_3: LM1.4, RM1.13
ML0_4: LM1.5, RM1.12
ML0_5: LM1.6, RM1.11
ML0_6: LM1.7, RM1.10
ML0_7: LM1.8, RM1.9
ML1_0: LM2.1, RM2.16
ML1_1: LM2.2, RM2.15
ML1_2: LM2.3, RM2.14
ML1_3: LM2.4, RM2.13
ML1_4: LM2.5, RM2.12
ML1_5: LM2.6, RM2.11
ML1_6: LM2.7, RM2.10
ML1_7: LM2.8, RM2.9
ML2_0: LM3.1, RM3.16
ML2_1: LM3.2, RM3.15
ML2_2: LM3.3, RM3.14
ML2_3: LM3.4, RM3.13
ML2_4: LM3.5, RM3.12
ML2_5: LM3.6, RM3.11
ML2_6: LM3.7, RM3.10
ML2_7: LM3.8, RM3.9
P2P: U6.4, U15.6
P4P: U6.12, U18.2
RTCCE: J3.1, U16.5
RTCIO: J3.3, U16.6
RTCSCLK: J3.2, U16.7
RTCX1: U16.2, X3.1
RTCX2: U16.3, X3.2
RXD: U8.12, U14.2
RXD2: U8.9, U17.2
S1RXD: DB9A.2, JP1.2, JP1.5
S1TXD: DB9A.3, JP1.1, JP1.6
S2RXD: DB9B.2, JP2.2, JP2.5
S2TXD: DB9B.3, JP2.1, JP2.6
SELP: R4.2, U6.8
SIN: JP1.4, U8.13
SIN2: JP2.4, U8.8
SOUT: JP1.3, U8.14
SOUT2: JP2.3, U8.7
SWN0: RNP.2, SW1.1, U9.2
SWN1: RNP.3, SW1.2, U9.4
SWN2: RNP.4, SW1.3, U9.6
SWN3: RNP.5, SW1.4, U9.8
SWN4: RNP.6, SW1.5, U9.11
SWN5: RNP.7, SW1.6, U9.13
SWN6: RNP.8, SW1.7, U9.15
SWN7: RNP.9, SW1.8, U9.17
TXD: U8.11, U14.6
TXD2: U8.10, U17.6
VBAT: BT1.1, U16.1
VCC: C6.1, C7.1, C8.1, C9.1, C10.1, C11.1, C12.1, C13.1, C14.1, C15.1, C16.1, C17.1, C18.1, C19.1, C20.1, C21.1, C22.1, C23.1, J1.a1, J1.a2, J1.b1, J1.b2, J1.c1, J1.c2, RNP.1, RP1.1, U1.14, U2.6, U2.16, U3.6, U3.16, U4.6, U4.16, U5.14, U6.14, U7.1, U7.7, U7.9, U7.10, U7.16, U8.16, U9.20, U10.20, U11.20, U12.20, U13.20, U14.8, U14.10, U14.12, U15.14, U16.8, U17.8, U17.10, U17.12, U18.14, X2.14
VMN: C5.1, U8.6
VPN: C4.1, U8.2

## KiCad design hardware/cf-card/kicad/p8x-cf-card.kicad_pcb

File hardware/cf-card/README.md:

# CF-IDE Card

> **Theory of operation:** [p8x-cf-card-theory.md](p8x-cf-card-theory.md) — deep walkthrough of inputs/outputs, signal flow, and logic.

Adds mass storage: a CompactFlash card running in **8-bit True IDE mode**,
memory-mapped into the I/O page at **$FF10–$FF17**. This is what lets the P8X load
an OS and a filesystem from removable media instead of living entirely in ROM.

> **Rev B (2026-09-19): two drives.** The routed KiCad board in
> [`kicad/`](kicad/README.md) (not yet fabricated) carries a second, fully decoded
> CF drive: drive 0 at `$FF10–$FF17` on header J2, drive 1 at `$FF18–$FF1F` on
> header J5, each with its own 74245 buffer, strobe glue, pull-ups and activity
> LED (master/slave on one channel was rejected as unreliable for True IDE CF).
> **Software follow-up:** the firmware CF driver and the emulator select drive 1
> with the device bit on `$FF10–$FF17`, so drive 1 on this card needs a
> drive-selectable port base first; drive 0 works unchanged. The chip-by-chip text
> below describes the drive-0 circuit.

> This README describes the circuit as actually built in
> [`generators/gen_eagle.py`](../../generators/gen_eagle.py). For the storage
> software stack see [p8x-cf-os-design.md](p8x-cf-os-design.md) and
> [p8xfs-v2-hierarchical.md](p8xfs-v2-hierarchical.md); for bus pins see
> [p8x-bus-definition.md](../backplane/p8x-bus-definition.md).

## Chip inventory

| Ref | Device | Role |
|-----|--------|------|
| U1 | 74245 | Bidirectional data-bus transceiver (P8X bus ↔ CF data) |
| U2 | 7430 | 8-input NAND — I/O page ($FFxx) detector |
| U3 | 74138 | DOE decoder (read enable) |
| U4 | 74138 | DLD decoder (write strobe) |
| U5 | 74HCT14 | Schmitt inverters — strobe/select conditioning |
| U6, U7 | 7410 | 3-input NAND — register/select decode and -IOR/-IOW gating |
| U8 | 74HCT08 | AND glue — chip-select combine, activity LED |
| J2 | 40-pin IDE | CompactFlash / IDE connector |

## How it works

### Address decode ($FF10–$FF17)
U2 (7430) detects the `$FFxx` page. The CF task-file registers occupy
`$FF10–$FF17`; the low address lines A0–A4 select the individual IDE register, and
the 7410 NANDs (U6/U7) combine the page hit with A3/A4 to produce the two True-IDE
chip selects **-CS0** (command block) and **-CS1** (control block). U8 ANDs them
into a single `-CFSEL` "this card is addressed" signal.

### Read / write strobes
DOE code 7 (`-RD`) and DLD code 7 (`-MEMW`) are decoded by U3/U4. Gated with the
clock and `-CFSEL` through U5/U7, they become the IDE bus strobes **-IOR** (I/O
read) and **-IOW** (I/O write) on the connector. These are the standard True-IDE
timing signals the CF card expects.

### Data path
A single **74245** (U1) bridges the P8X data bus and the CF data lines (the low 8
bits — this is 8-bit mode, so the high byte of the IDE 16-bit data path is unused).
Its **direction** follows `-IOR` (read = drive toward the P8X bus) and it is
**enabled** only when the card is selected (`-CFOE`), so it never contends with
other bus drivers.

### Status lines
The CF's open-drain status lines — **IORDY**, **-PDIAG**, **-DASP** — are pulled up
through a SIP resistor network (RN1). `-DASP` (drive active / slave present) also
drives the activity LED.

### Reset
The backplane **-RES** is wired to the IDE connector's reset pin, so the CF card is
reset together with the rest of the machine.

## Bus codes this card owns
- **DOE:** 7 = read (drives D0–D7 when `$FF10–$FF17` is addressed)
- **DLD:** 7 = write (`MEMW`) — shared decode convention with memory & I/O cards

The CF card, memory card, and I/O card all decode the same DOE=7 / DLD=7 codes;
the address decode (which page/region) is what keeps exactly one of them active per
cycle.

## LEDs
PWR (green), ACT (yellow — card selected / access in progress), DASP (green — CF
present and active).

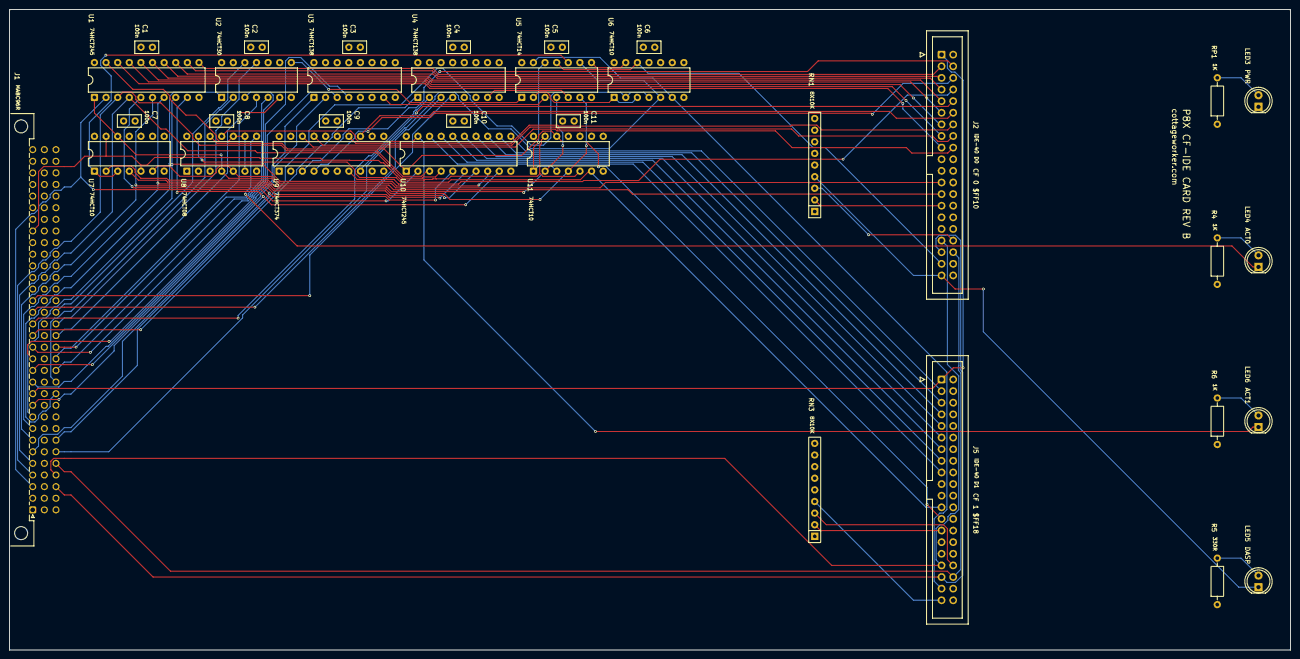
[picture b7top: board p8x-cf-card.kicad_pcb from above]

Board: 4 copper layers, 280.0 x 140.0 mm, 35 parts (0 on the bottom side), 85 nets.

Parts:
C1, C2, C3, C4, C5, C6, C7, C8, C9, C10, C11: 100nF; C_Disc_D5.0mm_W2.5mm_P2.50mm
J1: MABC96R; DIN41612_C_3x32_Male_Horizontal_THT
J2: IDE-40 D0; IDC-Header_2x20_P2.54mm_Vertical
J5: IDE-40 D1; IDC-Header_2x20_P2.54mm_Vertical
LED3, LED5: GRN; LED_D5.0mm
LED4, LED6: YEL; LED_D5.0mm
R4, R6: 1K; R_Axial_DIN0207_L6.3mm_D2.5mm_P10.16mm_Horizontal
R5: 330R; R_Axial_DIN0207_L6.3mm_D2.5mm_P10.16mm_Horizontal
RN1, RN3: 8X10K; R_Array_SIP9
RP1: 1K; R_Axial_DIN0207_L6.3mm_D2.5mm_P10.16mm_Horizontal
U1, U10: 74HCT245; DIP-20_W7.62mm
U2: 74HCT30; DIP-14_W7.62mm
U3, U4: 74HCT138; DIP-16_W7.62mm
U5: 74HCT14; DIP-14_W7.62mm
U6, U7, U11: 74HCT10; DIP-14_W7.62mm
U8: 74HCT08; DIP-14_W7.62mm
U9: 74HCT374; DIP-20_W7.62mm

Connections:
-CFOE: U1.19, U8.6, U8.9, U8.10
-CFOE1: LED6.1, U8.11, U10.19
-CS0: J2.37, U5.11, U6.12
-CS1: J5.37, U5.13, U6.6
-DASP: J2.39, LED5.1, RN1.4
-DASP1: J5.39, RN3.4
-IOR: J2.25, U1.1, U7.12, U8.4
-IOR1: J5.25, U8.12, U10.1, U11.12
-IOW: J2.23, U7.6, U8.5
-IOW1: J5.23, U8.13, U11.6
-MEMW: U4.7, U5.5
-PDIAG: J2.34, RN1.3
-PDIAG1: J5.34, RN3.3
-RD: U3.7, U5.3
-RES: J1.a11, J2.1, J5.1
A0: J1.c3, J2.35, J5.35
A1: J1.c4, J2.33, J5.33
A2: J1.c5, J2.36, J5.36
A3: J1.c6, U5.9, U6.5
A3N: U5.8, U6.13
A4: J1.c7, U6.2, U6.4
A8: J1.c11, U2.1
A9: J1.c12, U2.2
A10: J1.c13, U2.3
A11: J1.c14, U2.4
A12: J1.c15, U2.5
A13: J1.c16, U2.6
A14: J1.c17, U2.11
A15: J1.c18, U2.12
ACTK: LED4.1, U8.8
CF1D0: J5.17, U10.18
CF1D1: J5.15, U10.17
CF1D2: J5.13, U10.16
CF1D3: J5.11, U10.15
CF1D4: J5.9, U10.14
CF1D5: J5.7, U10.13
CF1D6: J5.5, U10.12
CF1D7: J5.3, U10.11
CFD0: J2.17, U1.18
CFD1: J2.15, U1.17
CFD2: J2.13, U1.16
CFD3: J2.11, U1.15
CFD4: J2.9, U1.14
CFD5: J2.7, U1.13
CFD6: J2.5, U1.12
CFD7: J2.3, U1.11
CFD8: J2.4, U9.3
CFD9: J2.6, U9.4
CFD10: J2.8, U9.7
CFD11: J2.10, U9.8
CFD12: J2.12, U9.13
CFD13: J2.14, U9.14
CFD14: J2.16, U9.17
CFD15: J2.18, U9.18
CLKB: J1.a25, U7.5, U7.13, U11.5, U11.13
D0: J1.a3, U1.2, U10.2
D1: J1.a4, U1.3, U10.3
D2: J1.a5, U1.4, U10.4
D3: J1.a6, U1.5, U10.5
D4: J1.a7, U1.6, U10.6
D5: J1.a8, U1.7, U10.7
D6: J1.a9, U1.8, U10.8
D7: J1.a10, U1.9, U10.9
DLD0: J1.a16, U4.1
DLD1: J1.a17, U4.2
DLD2: J1.a18, U4.3
DLD3: J1.a19, U4.4
DOE0: J1.a12, U3.1
DOE1: J1.a13, U3.2
DOE2: J1.a14, U3.3
DOE3: J1.a15, U3.4
GND: C1.2, C2.2, C3.2, C4.2, C5.2, C6.2, C7.2, C8.2, C9.2, C10.2, C11.2, J1.a31, J1.a32, J1.b3, J1.b5, J1.b7, J1.b9, J1.b11, J1.b13, J1.b15, J1.b17, J1.b19, J1.b21, J1.b23, J1.b25, J1.b31, J1.b32, J1.c31, J1.c32, J2.2, J2.19, J2.22, J2.24, J2.26, J2.28, J2.30, J2.40, J5.2, J5.19, J5.22, J5.24, J5.26, J5.28, J5.30, J5.40, LED3.1, U1.10, U2.7, U3.5, U3.8, U4.5, U4.8, U5.7, U6.7, U6.9, U6.10, U6.11, U7.7, U7.9, U7.10, U7.11, U8.1, U8.2, U8.7, U9.10, U9.11, U10.10, U11.7, U11.9, U11.10, U11.11
IOPG: U2.8, U5.1
IOPGP: U5.2, U6.1, U6.3
IORDY: J2.27, RN1.2
IORDY1: J5.27, RN3.2
LEDAC: LED4.2, R4.2
LEDAC1: LED6.2, R6.2
LEDDA: LED5.2, R5.2
LEDP: LED3.2, RP1.2
RDP: U5.4, U7.2, U11.2
SELP: U5.10, U7.1, U7.3
SELP1: U5.12, U11.1, U11.3
VCC: C1.1, C2.1, C3.1, C4.1, C5.1, C6.1, C7.1, C8.1, C9.1, C10.1, C11.1, J1.a1, J1.a2, J1.b1, J1.b2, J1.c1, J1.c2, J2.29, J2.38, J5.29, J5.38, R4.1, R5.1, R6.1, RN1.1, RN3.1, RP1.1, U1.20, U2.14, U3.6, U3.16, U4.6, U4.16, U5.14, U6.14, U7.14, U8.14, U9.1, U9.20, U10.20, U11.14
WRP: U5.6, U7.4, U11.4
